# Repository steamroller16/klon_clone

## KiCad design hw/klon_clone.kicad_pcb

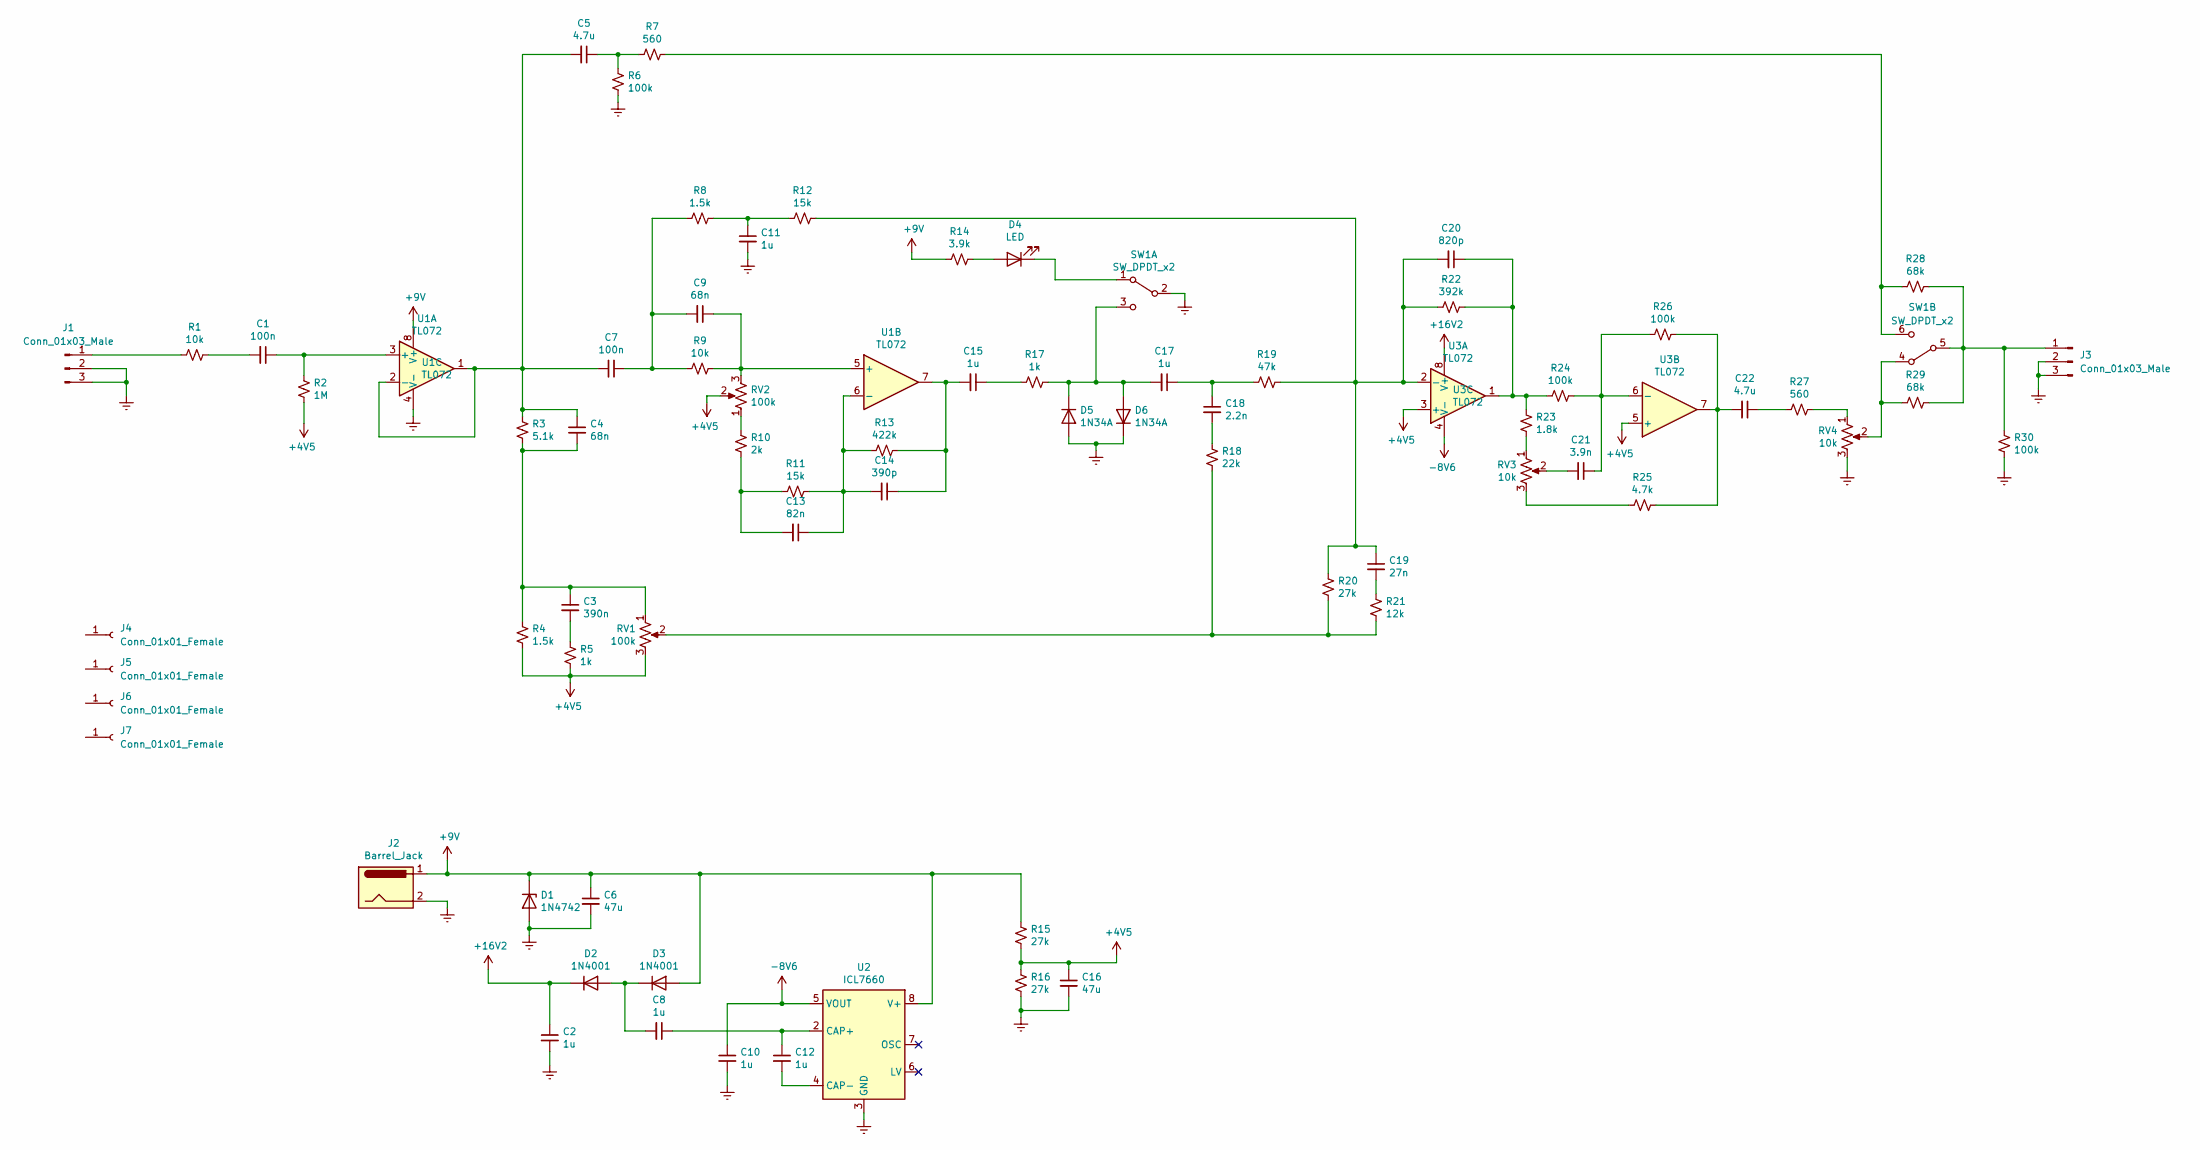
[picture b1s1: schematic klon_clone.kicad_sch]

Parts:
C1, C7: 100n; C_Rect_L13.0mm_W5.0mm_P10.00mm_FKS3_FKP3_MKS4
C2, C8, C10, C12: 1u; C_0805_2012Metric_Pad1.18x1.45mm_HandSolder
C3: 390n; C_Axial_L19.0mm_D9.5mm_P25.00mm_Horizontal
C4, C9: 68n; C_Axial_L5.1mm_D3.1mm_P15.00mm_Horizontal
C5, C22: 4.7u; CP_Radial_D5.0mm_P2.00mm
C6, C16: 47u; CP_Radial_D8.0mm_P5.00mm
C11, C15, C17: 1u; C_Axial_L17.5mm_W7.8mm_P7.5mm_Horizontal
C13: 82n; C_Rect_L10.3mm_W5.0mm_P7.50mm_MKS4
C14: 390p; C_Rect_L10.0mm_W4.0mm_P7.50mm_MKS4
C18: 2.2n; C_Rect_L18.0mm_W7.0mm_P15.00mm_FKS3_FKP3
C19: 27n; C_Rect_L10.3mm_W4.5mm_P7.50mm_MKS4
C20: 820p; C_Rect_L13.0mm_W4.0mm_P10.00mm_FKS3_FKP3_MKS4
C21: 3.9n; C_Rect_L16.5mm_W5.0mm_P15.00mm_MKT
D1: 1N4742; D_DO-41_SOD81_P10.16mm_Horizontal
D2, D3: 1N4001; D_DO-41_SOD81_P10.16mm_Horizontal
D4: LED; LED_D5.0mm
D5, D6: 1N34A; D_DO-35_SOD27_P10.16mm_Horizontal
J1, J3: Conn_01x03_Male; PinHeader_1x03_P2.54mm_Vertical
J2: Barrel_Jack; PinHeader_1x02_P2.54mm_Vertical
J4, J5, J6, J7: Conn_01x01_Female; MountingHole_3.2mm_M3
R1, R9: 10k; R_0805_2012Metric_Pad1.20x1.40mm_HandSolder
R2: 1M; R_0805_2012Metric_Pad1.20x1.40mm_HandSolder
R3: 5.1k; R_0805_2012Metric_Pad1.20x1.40mm_HandSolder
R4, R8: 1.5k; R_0805_2012Metric_Pad1.20x1.40mm_HandSolder
R5, R17: 1k; R_0805_2012Metric_Pad1.20x1.40mm_HandSolder
R6, R24, R26, R30: 100k; R_0805_2012Metric_Pad1.20x1.40mm_HandSolder
R7, R27: 560; R_0805_2012Metric_Pad1.20x1.40mm_HandSolder
R10: 2k; R_0805_2012Metric_Pad1.20x1.40mm_HandSolder
R11, R12: 15k; R_0805_2012Metric_Pad1.20x1.40mm_HandSolder
R13: 422k; R_0805_2012Metric_Pad1.20x1.40mm_HandSolder
R14: 3.9k; R_0805_2012Metric_Pad1.20x1.40mm_HandSolder
R15, R16, R20: 27k; R_0805_2012Metric_Pad1.20x1.40mm_HandSolder
R18: 22k; R_0805_2012Metric_Pad1.20x1.40mm_HandSolder
R19: 47k; R_0805_2012Metric_Pad1.20x1.40mm_HandSolder
R21: 12k; R_0805_2012Metric_Pad1.20x1.40mm_HandSolder
R22: 392k; R_0805_2012Metric_Pad1.20x1.40mm_HandSolder
R23: 1.8k; R_0805_2012Metric_Pad1.20x1.40mm_HandSolder
R25: 4.7k; R_0805_2012Metric_Pad1.20x1.40mm_HandSolder
R28, R29: 68k; R_0805_2012Metric_Pad1.20x1.40mm_HandSolder
RV1, RV2: 100k; PinHeader_1x03_P2.54mm_Vertical
RV3, RV4: 10k; PinHeader_1x03_P2.54mm_Vertical
SW1: SW_DPDT_x2; PinHeader_1x06_P2.54mm_Vertical
U1, U3: TL072; SO-8_5.3x6.2mm_P1.27mm
U2: ICL7660; SO-8_5.3x6.2mm_P1.27mm

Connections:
+4V5: C16.1, R2.2, R4.2, R5.2, R15.2, R16.1, RV1.3, RV2.2, U3.3 (+), U3.5 (+)
+9V: C6.1, D1.1 (K), D3.2 (A), J2.1, R14.2, R15.1, U1.8 (V+), U2.8 (V+)
+16V2: C2.1, D2.1 (K), U3.8 (V+)
-8V6: C10.1, U2.5 (VOUT), U3.4 (V-)
Earth: C2.2, C6.2, C10.2, C11.2, C16.2, D1.2 (A), D5.2 (A), D6.1 (K), J1.2, J1.3, J2.2, J3.2, J3.3, R6.2, R16.2, R30.2, RV4.3, SW1.2 (B), U1.4 (V-), U2.3 (GND)
unnamed: C1.1, R2.1, U1.3 (+)
unnamed: C1.2, R1.1
unnamed: C3.1, C4.2, R3.2, R4.1, RV1.1
unnamed: C3.2, R5.1
unnamed: C4.1, C5.2, C7.2, R3.1, U1.1, U1.2 (-)
unnamed: C5.1, R6.1, R7.2
unnamed: C7.1, C9.2, R8.2, R9.2
unnamed: C8.2, D2.2 (A), D3.1 (K)
unnamed: C9.1, R9.1, RV2.3, U1.5 (+)
unnamed: C11.1, R8.1, R12.2
unnamed: C8.1, C12.1, U2.2 (CAP+)
unnamed: C12.2, U2.4 (CAP-)
unnamed: C13.1, C14.2, R11.1, R13.2, U1.6 (-)
unnamed: C13.2, R10.2, R11.2
unnamed: C14.1, C15.2, R13.1, U1.7
unnamed: C15.1, R17.2
unnamed: C17.1, C18.1, R19.2
unnamed: C17.2, D5.1 (K), D6.2 (A), R17.1, SW1.3 (C)
unnamed: C18.2, R18.1
unnamed: C19.1, C20.2, R12.1, R19.1, R20.1, R22.2, U3.2 (-)
unnamed: C19.2, R21.1
unnamed: C20.1, R22.1, R23.1, R24.2, U3.1
unnamed: C21.1, R24.1, R26.2, U3.6 (-)
unnamed: C21.2, RV3.2
unnamed: C22.1, R27.2
unnamed: C22.2, R25.1, R26.1, U3.7
unnamed: D4.1 (K), SW1.1 (A)
unnamed: D4.2 (A), R14.1
unnamed: J1.1, R1.2
unnamed: J3.1, R28.1, R29.1, R30.1, SW1.5 (B)
unnamed: R10.1, RV2.1
unnamed: R18.2, R20.2, R21.2, RV1.2
unnamed: R23.2, RV3.1
unnamed: R25.2, RV3.3
unnamed: R27.1, RV4.1
unnamed: R7.1, R28.2, SW1.6 (C)
unnamed: R29.2, RV4.2, SW1.4 (A)

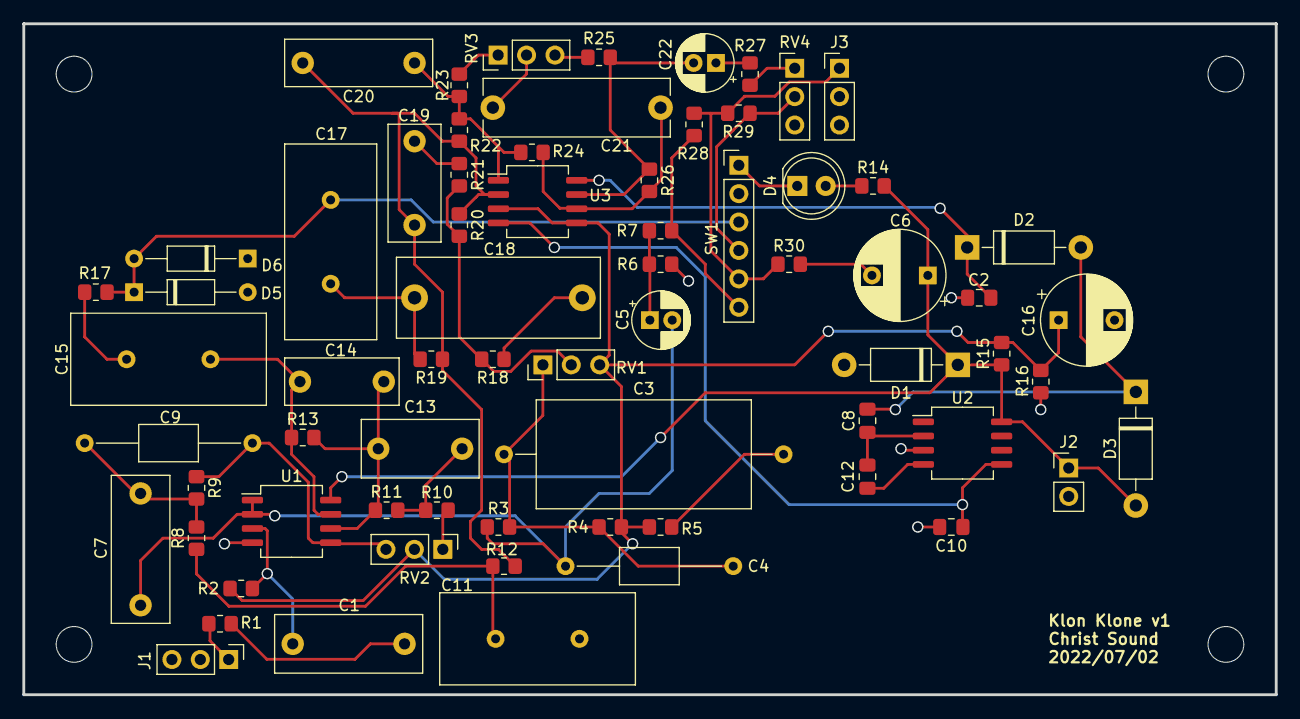
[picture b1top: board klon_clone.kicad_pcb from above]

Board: 2 copper layers, 112.0 x 60.0 mm, 73 parts (0 on the bottom side), 42 nets.

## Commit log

2021-12-20 Created new kicad project from oshpark_jlcpcb template.
2021-12-20 Placed components on schematic.
2021-12-20 Added power symbols and connectors.
2021-12-21 Schematic wiring done.
2021-12-21 Component values set.
2021-12-23 Added ltspice simulation schematic.
2021-12-23 Added notes.txt.
2022-02-08 Updated to KiCad 6.0
2022-04-10 Checking in.
2022-04-10 Annotated sch.
2022-04-11 Added all footprints but switch footprint.
2022-04-11 Added SOIC Opamp footprints.
    Added tenative footprints for opamps. Double check we have right package. Need to add footprint for Power supply IC>
2022-04-18 Assigned SO8 to ICL7660
2022-04-18 Added project specific footprint and parts libraries (kicad_parts_library from github)
2022-04-18 Assigned new cap footprint for 1uF
2022-04-18 Updated J1/J3 footprints and symbols. Initial layout placement.
2022-06-26 Layout Updates
    Started routing traces on layer 1
2022-07-02 PCB Updates
    Almost completed board. FInished traces, poured GND plane on layer2, added names and mounting holes.
2022-07-02 Update fp-info-cache
2022-08-02 Refilled zones before generating gerbers.
2022-08-02 Moved hidden connector silkscreen items inside board outline.
2022-08-02 Added gerber files submitted for production: v1_20220702
